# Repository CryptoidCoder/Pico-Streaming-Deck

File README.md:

# Pico Streaming Deck

## To Use:
- Hold down the `bootsel` button and plug in your Pico (to a computer) - this will then show as a Usb storage device, 
- Copy the `.uf2` file onto tis device. It should unmount itself,
- Then go into your ide [(I recommended thonny)](https://www.raspberrypi.org/documentation/pico/getting-started/)
- Then open the .py files, and save them to the board.
- ***OPTIONAL*** - If you want you can rename the `StreamDeck.py` to `code.py` to make it run on boot
- Now you have the streaming deck code.

## Circuit Diagram:
- Create a circuitboard like this.
- Feel free to interchange buttons for mechanical keyboard keys.
- Have fun and make it yours! (Maybe make a case?)
.jpg)

## Explanation:
You can change the code to whatever you want [This will be useful](https://github.com/adafruit/Adafruit_CircuitPython_HID/blob/master/adafruit_hid/keycode.py) but this is what the defaults are:
- The switch moves between desktop environments (`Ctrl+Win+D/Left_Arrow/Right_Arrow`) & flashes the LED's - To see what desktop envrionments you have Press `Win+Tab`
- Button0 (the furthest Left on the diagram) moves to desktop (`Win+D`) & flashes the LED's
- Button1 moves between windows - (`Alt+Tab`)
- Button2 opens the Program Menu (`Win`)
- Button3 turns on streamer mode in Discord (`Ctrl+Shift+F1`) - You will need to set this custom shortcut in Discord for this to work
- Button4 currently does nothing.

## With Thanks To:
[JBDynamics for providing the Pico library for Eagle](https://www.raspberrypi.org/forums/viewtopic.php?t=302397#p1814462)
[Here is a direct download link](https://www.raspberrypi.org/forums/download/file.php?id=44669)

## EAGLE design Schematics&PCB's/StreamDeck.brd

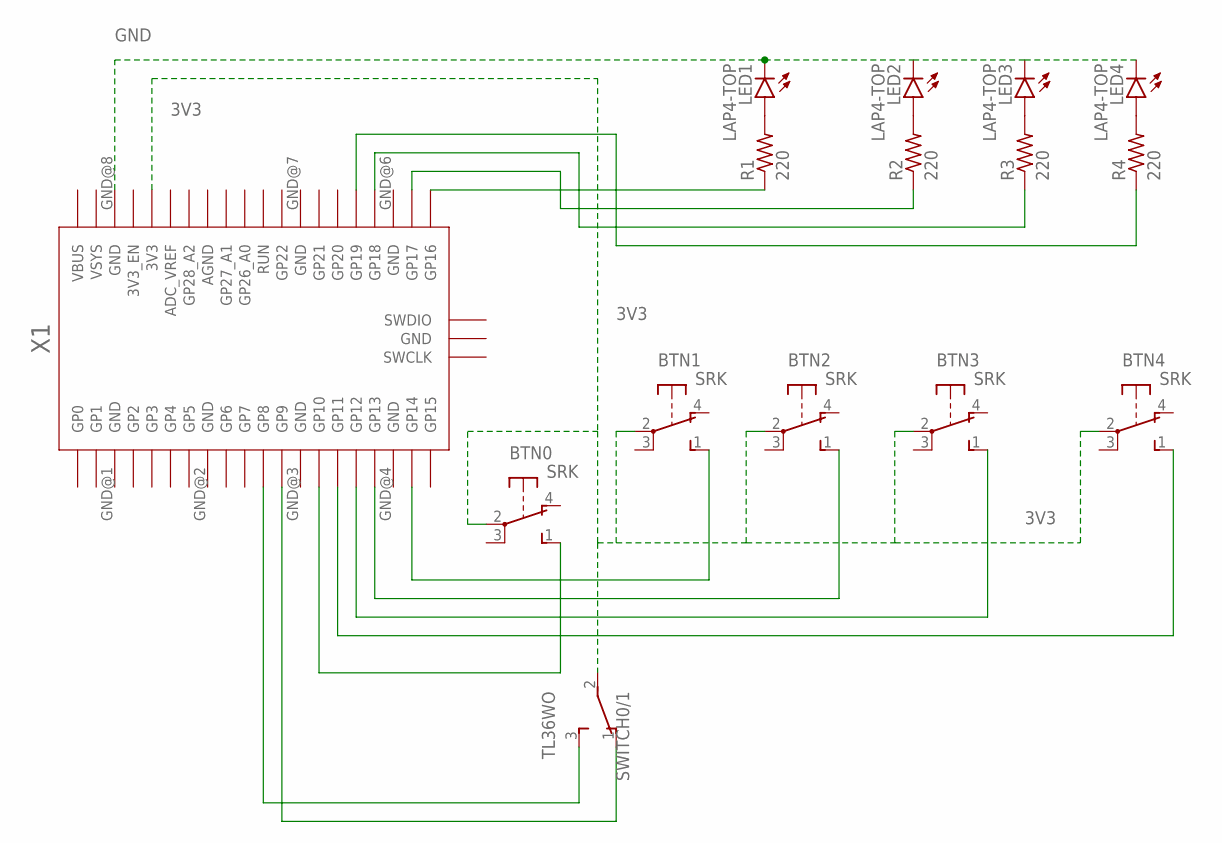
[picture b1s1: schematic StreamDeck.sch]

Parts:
BTN0, BTN1, BTN2, BTN3, BTN4: SRK
LED1, LED2, LED3, LED4: LAP4-TOP; P47F-TOP
R1, R2, R3, R4: 220; 0204/5
SWITCH0/1: TL36WO; TL3XWO
X1: RPI_PICO_IG-SMD; RPI_PICO

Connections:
3V3: BTN0.2, BTN1.2, BTN2.2, BTN3.2, BTN4.2, SWITCH0/1.2, X1.3V3
GND: LED1.C, LED2.C, LED3.C, LED4.C, X1.GND@8 (GND)
unnamed: LED1.A, R1.2
unnamed: LED2.A, R2.2
unnamed: LED3.A, R3.2
unnamed: LED4.A, R4.2
unnamed: BTN0.1 (S), X1.GP10
unnamed: R1.1, X1.GP16
unnamed: R2.1, X1.GP17
unnamed: R3.1, X1.GP18
unnamed: R4.1, X1.GP19
unnamed: BTN1.1 (S), X1.GP14
unnamed: BTN3.1 (S), X1.GP12
unnamed: BTN2.1 (S), X1.GP13
unnamed: BTN4.1 (S), X1.GP11
unnamed: SWITCH0/1.1 (O), X1.GP9
unnamed: SWITCH0/1.3 (S), X1.GP8

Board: 2 copper layers, 15 parts (0 on the bottom side), 17 nets, no tracks yet.

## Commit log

2021-03-13 Added Labelled Circuit Diagram
2021-03-13 Added Explanation
2021-03-14 Added Schematic & PCB
2021-03-14 updates 1.1
2021-03-14 added pttt functionality
2021-05-30 Updates 3.0
